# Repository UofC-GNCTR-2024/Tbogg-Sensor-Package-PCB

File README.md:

# Tbogg-Sensor-Package-PCB
The sensor package (strain, temperature, vibration) for the 2024 UofC GNCTR tbogg. Designed as an R&amp;D intrastructure monitoring solution.

## Main Components

1. **2x** Strain Gauge Blocks
	* Ulimately reads one of these two strain gauges:
		1. [100x BF350-3AA](https://www.aliexpress.com/item/595240806.html)
		2. [10x BX120-2AA](https://www.aliexpress.com/item/1005003672107724.html)
	* Based on [this schematic](https://www.elecrow.com/strain-gauge-module-p-735.html)
	* Sensing via HX711 chip
2. **1x** On-PCB Temperature Sensor (STDS75DS2F)
	* I2C
3. **2x** In-Concrete Temperature Sensors
	* Thermistor-based
4. **1x** Vibration Sensor
	* Model: MPU-6050 Breakout
	* I2C Comms
5. I2C Optical Flow Sensor
6. Battery: 4x 18650
	* TODO: choose quantity, model, holder, and connection
	* In series
7. Battery Management System: probably the 3V3 buck-boost from the balloon project
	* TODO: more info
8. Wireless Comms: LoRa Wio E5
	* TODO: pull from balloon project
	* TODO: confirm that this model is good
9. Microcontroller Unit (MCU)
	* ESP32 Breakout

## Reference Links
* TODO: fill

## Revision Notes
* PCB orders will each recieve a new revision number. 
	* PCB orders will be in the format of "Rev1", "Rev2", etc.
	* GitHub Releases (and Tags) will be tagged in the format of `rev1`, `rev2`, etc.
* BOM changes on PCB orders should be documented as minor revisions.
	* Example: `rev1.1`, `rev1.2`, etc.

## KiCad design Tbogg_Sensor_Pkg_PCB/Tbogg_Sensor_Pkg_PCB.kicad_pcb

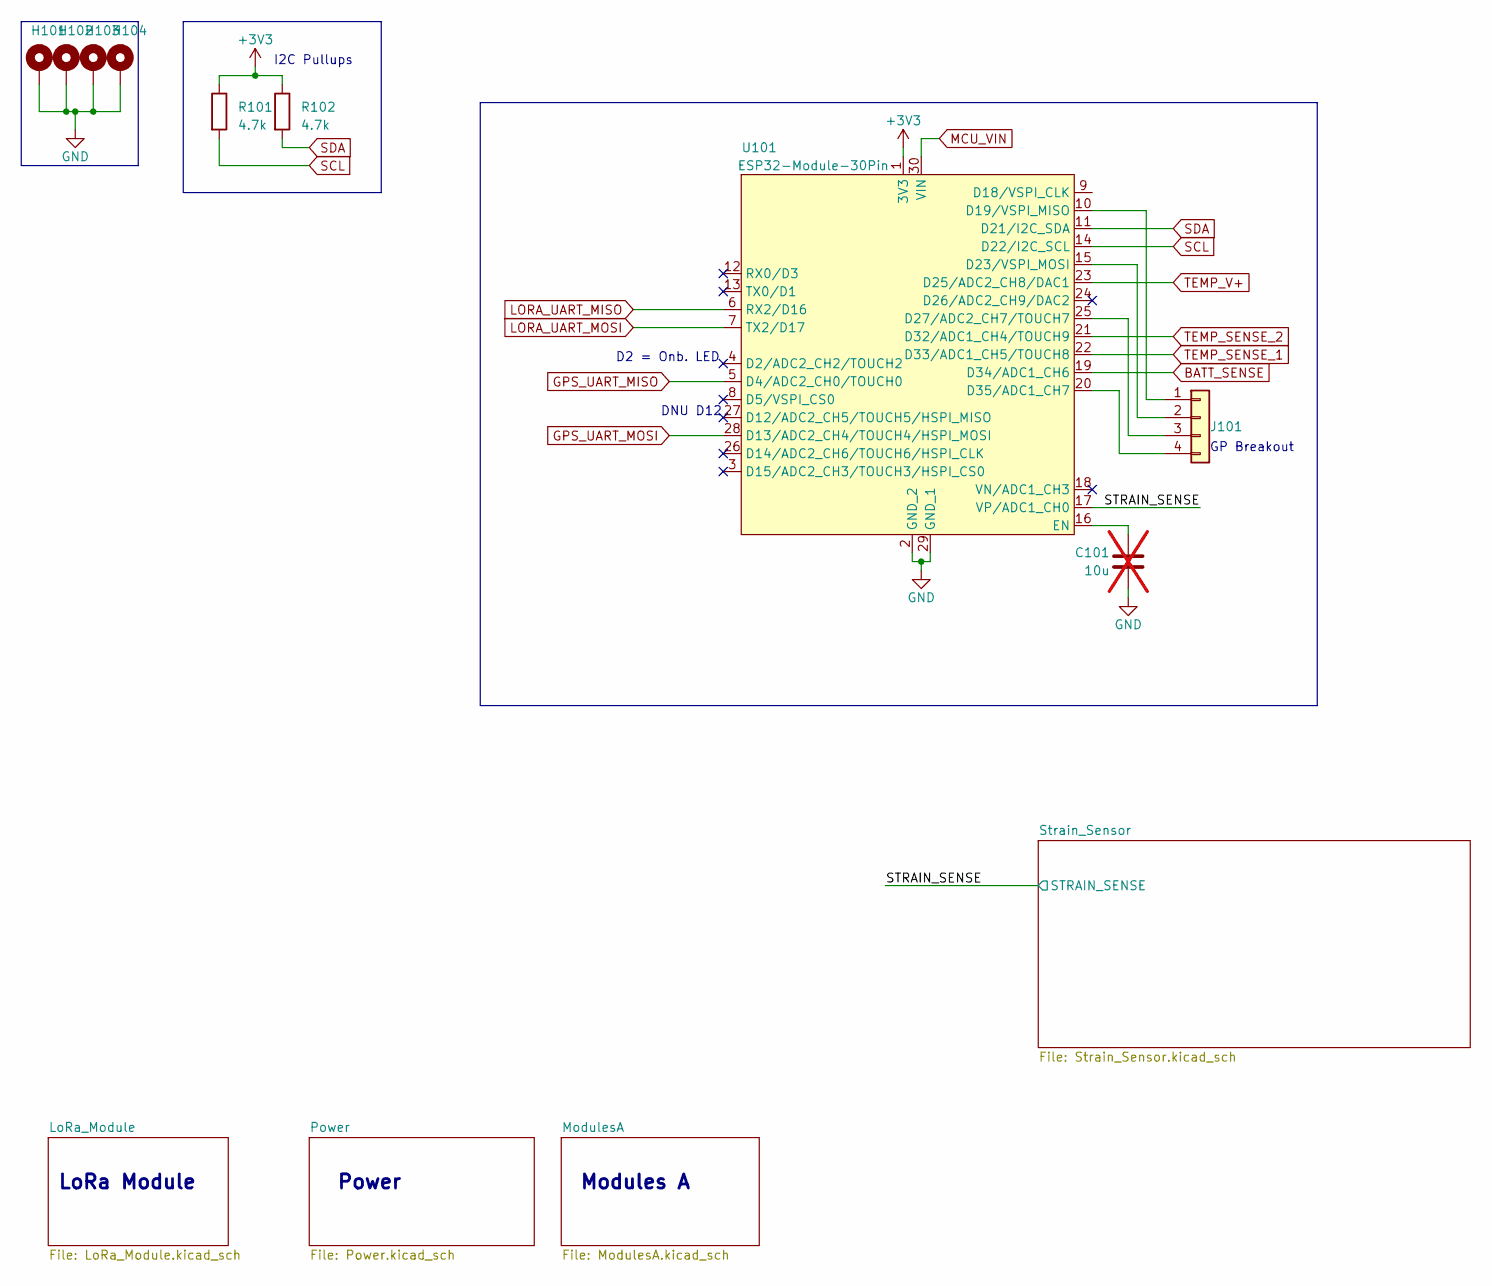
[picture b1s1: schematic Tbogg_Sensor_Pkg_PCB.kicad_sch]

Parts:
C101: 10u; C_1206_3216Metric_Pad1.33x1.80mm_HandSolder; not fitted
H101, H102, H103, H104: MountingHole_Pad; MountingHole_3.2mm_M3_DIN965_Pad
J101: Conn_01x04; PinHeader_1x04_P2.54mm_Vertical
R101, R102: 4.7k; R_1206_3216Metric_Pad1.30x1.75mm_HandSolder
U101: ESP32-Module-30Pin

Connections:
BATT_SENSE: U101.19 (D34/ADC1_CH6); also elsewhere on the board
GND: C101.2, H101.1, H102.1, H103.1, H104.1, U101.2 (GND_2), U101.29 (GND_1); also elsewhere on the board
GPS_UART_MISO: U101.5 (D4/ADC2_CH0/TOUCH0); also elsewhere on the board
GPS_UART_MOSI: U101.28 (D13/ADC2_CH4/TOUCH4/HSPI_MOSI); also elsewhere on the board
LORA_UART_MISO: U101.6 (RX2/D16); also elsewhere on the board
LORA_UART_MOSI: U101.7 (TX2/D17); also elsewhere on the board
MCU_VIN: U101.30 (VIN); also elsewhere on the board
unnamed: J101.1, U101.10 (D19/VSPI_MISO)
unnamed: J101.2, U101.15 (D23/VSPI_MOSI)
unnamed: J101.3, U101.25 (D27/ADC2_CH7/TOUCH7)
unnamed: J101.4, U101.20 (D35/ADC1_CH7)
unnamed: C101.1, U101.16 (EN)
SCL: R101.2, U101.14 (D22/I2C_SCL); also elsewhere on the board
SDA: R102.2, U101.11 (D21/I2C_SDA); also elsewhere on the board
TEMP_SENSE_1: U101.22 (D33/ADC1_CH5/TOUCH8); also elsewhere on the board
TEMP_SENSE_2: U101.21 (D32/ADC1_CH4/TOUCH9); also elsewhere on the board
TEMP_V+: U101.23 (D25/ADC2_CH8/DAC1); also elsewhere on the board

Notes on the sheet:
LoRa Module
GP Breakout
D2 = Onb. LED
Modules A
DNU D12
Power
I2C Pullups

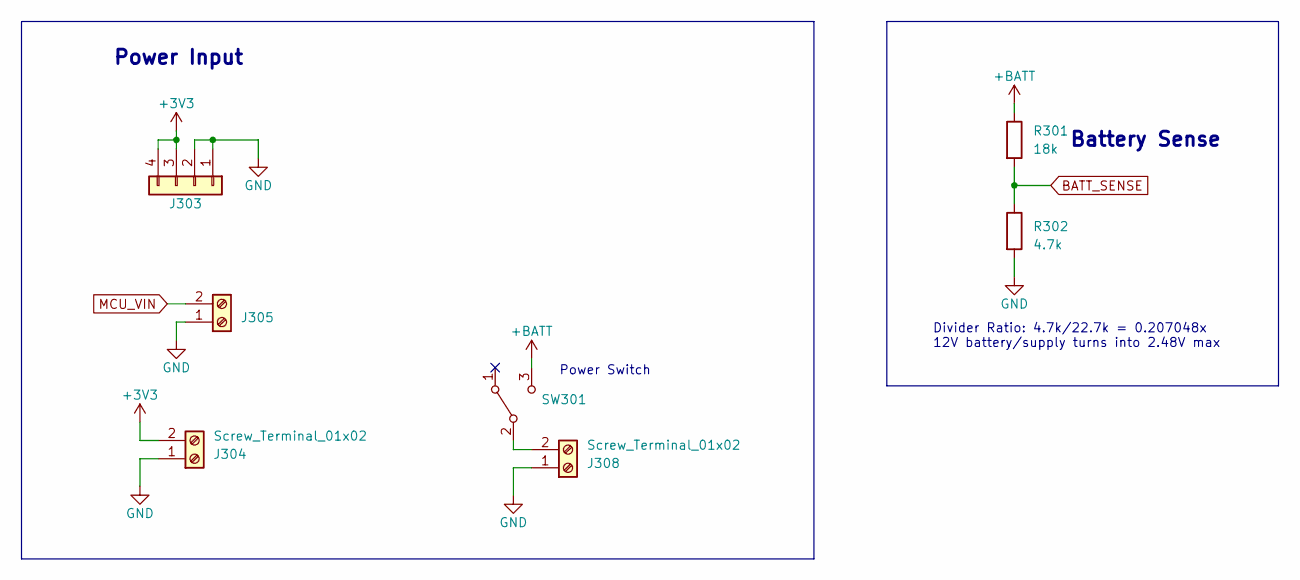
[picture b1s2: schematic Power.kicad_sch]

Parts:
J303: Conn_01x04; PinHeader_1x04_P2.54mm_Vertical
J304, J305, J308: Screw_Terminal_01x02; TerminalBlock_bornier-2_P5.08mm
R301: 18k; R_1206_3216Metric_Pad1.30x1.75mm_HandSolder
R302: 4.7k; R_1206_3216Metric_Pad1.30x1.75mm_HandSolder
SW301: SW_SPDT; SW_Slide_1P2T_CK_OS102011MS2Q

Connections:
+BATT: R301.1, SW301.3 (C)
BATT_SENSE: R301.2, R302.1; also elsewhere on the board
GND: J303.1, J303.2, J304.1, J305.1, J308.1, R302.2; also elsewhere on the board
MCU_VIN: J305.2; also elsewhere on the board
unnamed: J308.2, SW301.2 (B)

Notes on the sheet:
Divider Ratio: 4.7k/22.7k = 0.207048x 12V battery/supply turns into 2.48V max
Power Switch
Battery Sense
Power Input

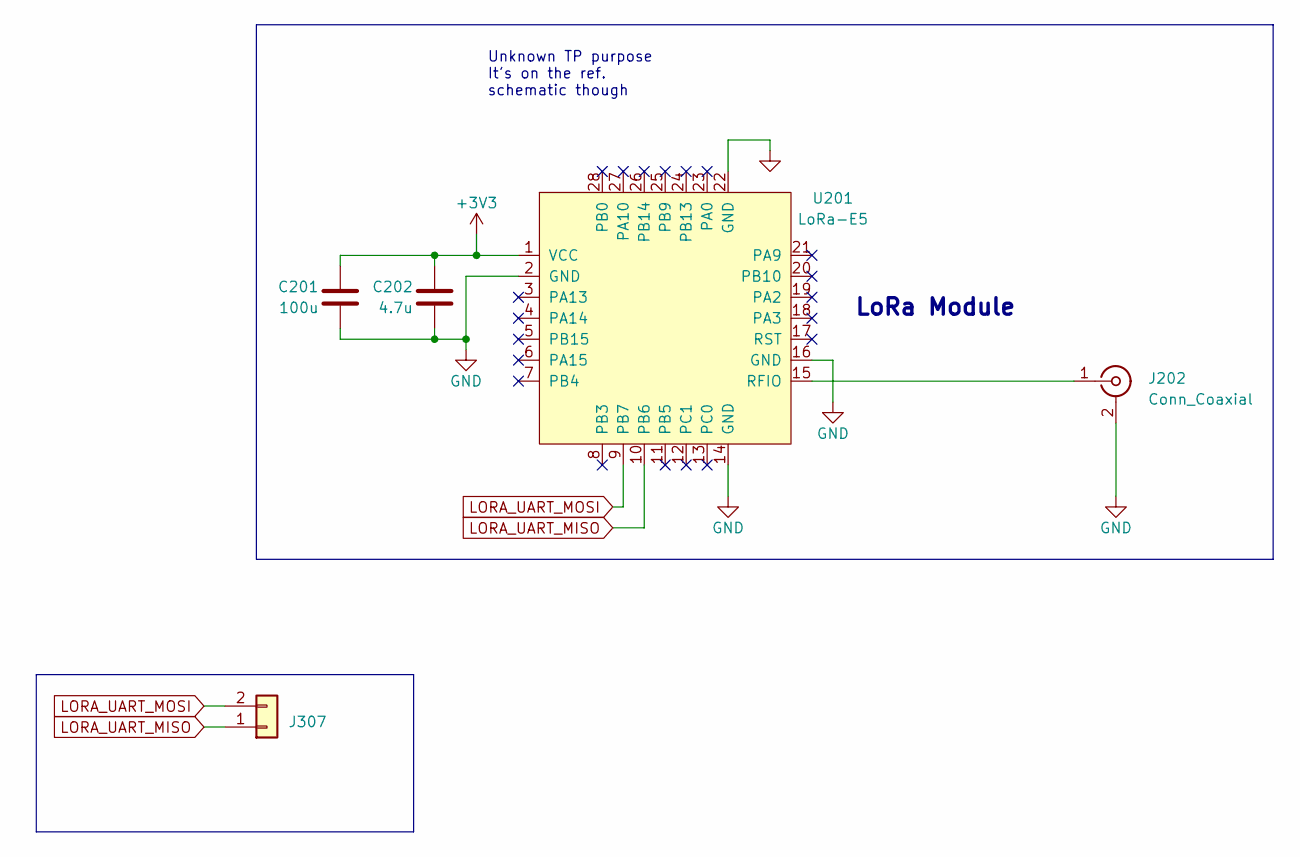
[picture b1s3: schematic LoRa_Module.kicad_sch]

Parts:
C201: 100u; C_1206_3216Metric_Pad1.33x1.80mm_HandSolder
C202: 4.7u; C_1206_3216Metric_Pad1.33x1.80mm_HandSolder
J202: Conn_Coaxial; SMA_Wurth_60312002114503_Vertical
J307: Conn_01x02; PinHeader_1x02_P2.54mm_Vertical
U201: LoRa-E5; LoRa-E5_HandSolder

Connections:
GND: C201.2, C202.2, J202.2 (Ext), U201.2 (GND), U201.14 (GND), U201.16 (GND), U201.22 (GND); also elsewhere on the board
LORA_UART_MISO: U201.10 (PB6); also elsewhere on the board
LORA_UART_MOSI: U201.9 (PB7); also elsewhere on the board
unnamed: J202.1 (In), U201.15 (RFIO)

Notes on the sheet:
Unknown TP purpose It's on the ref. schematic though
LoRa Module

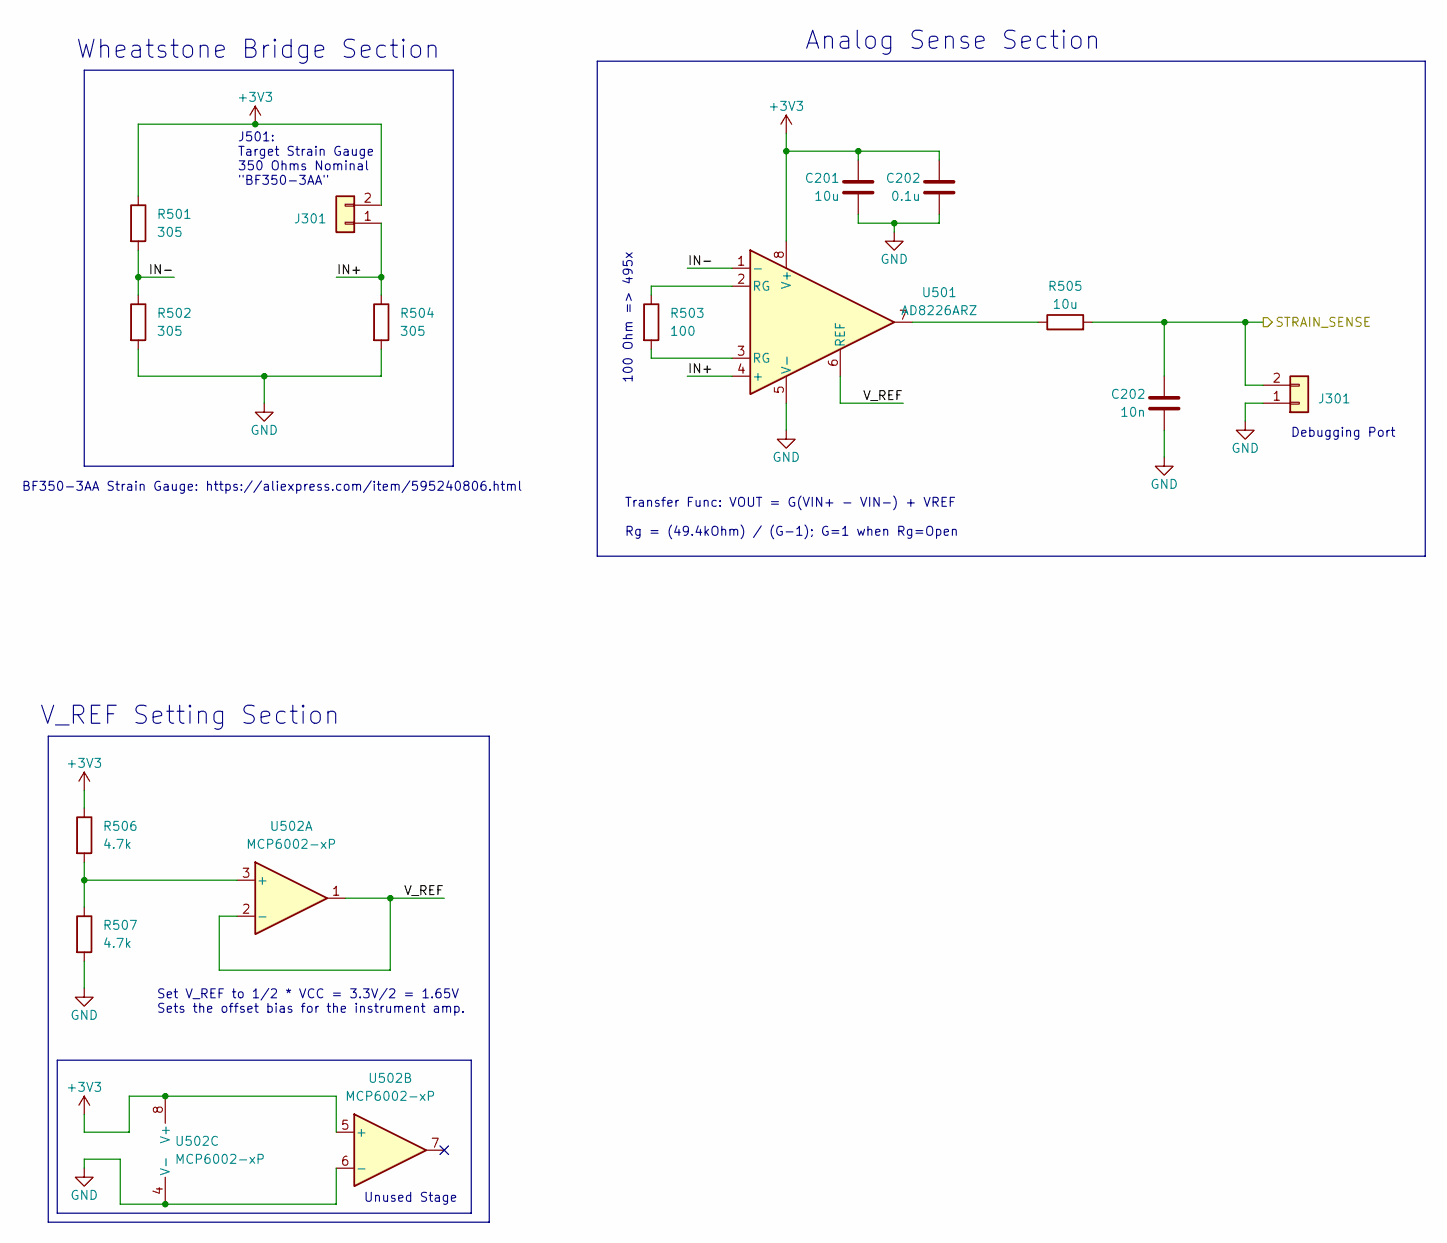
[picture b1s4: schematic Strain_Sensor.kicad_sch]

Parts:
C201: 10u; C_1206_3216Metric_Pad1.33x1.80mm_HandSolder
C202: 0.1u; C_1206_3216Metric_Pad1.33x1.80mm_HandSolder
J301: Conn_01x02; PinHeader_1x02_P2.54mm_Vertical
R501, R502, R504: 305; InactiveStrainGauge
R503: 100; R_1206_3216Metric_Pad1.30x1.75mm_HandSolder
R505: 10u; R_1206_3216Metric_Pad1.30x1.75mm_HandSolder
R506, R507: 4.7k; R_1206_3216Metric_Pad1.30x1.75mm_HandSolder
U501: AD8226ARZ; SO-8_3.9x4.9mm_P1.27mm
U502: MCP6002-xP; DIP-8_W7.62mm_LongPads

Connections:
/Strain_Sensor/IN+: R504.1, U501.4 (+); also elsewhere on the board
/Strain_Sensor/IN-: R501.2, R502.1, U501.1 (-)
/Strain_Sensor/V_REF: U501.6 (REF), U502.1, U502.2 (-)
GND: C201.2, C202.2, R502.2, R504.2, R507.2, U501.5 (V-), U502.4 (V-), U502.6 (-); also elsewhere on the board
unnamed: R503.1, U501.2 (RG)
unnamed: R503.2, U501.3 (RG)
unnamed: R505.1, U501.7
unnamed: R506.2, R507.1, U502.3 (+)

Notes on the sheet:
Unused Stage
J501: Target Strain Gauge 350 Ohms Nominal "BF350-3AA"
Debugging Port
V_REF Setting Section
Transfer Func: VOUT = G(VIN+ − VIN−) + VREF Rg = (49.4kOhm) / (G-1); G=1 when Rg=Open
100 Ohm => 495x
BF350-3AA Strain Gauge: https://aliexpress.com/item/595240806.html
Set V_REF to 1/2 * VCC = 3.3V/2 = 1.65V Sets the offset bias for the instrument amp.
Wheatstone Bridge Section
Analog Sense Section

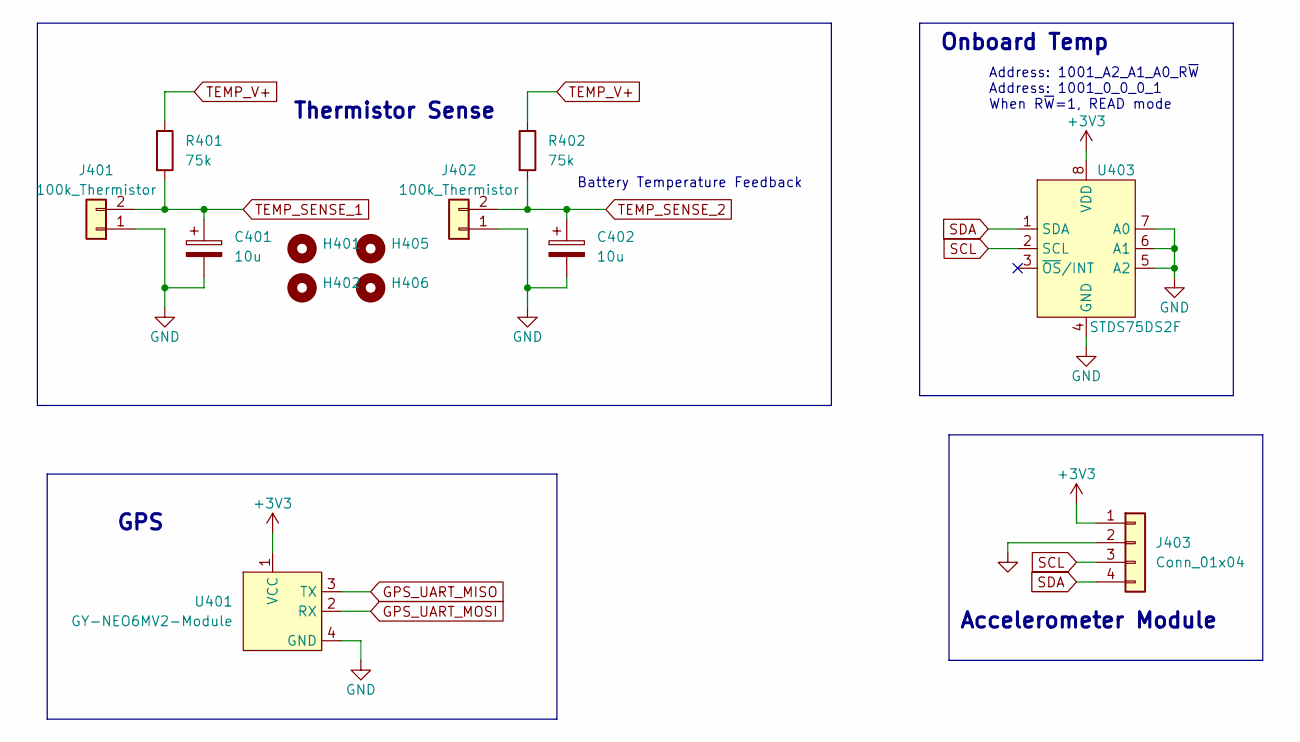
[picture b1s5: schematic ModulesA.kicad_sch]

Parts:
C401, C402: 10u; C_1206_3216Metric_Pad1.33x1.80mm_HandSolder
H401, H402, H405, H406: MountingHole; MountingHole_2mm
J401, J402: 100k_Thermistor; PinHeader_1x02_P2.54mm_Vertical
J403: Conn_01x04; PinHeader_1x04_P2.54mm_Vertical
R401, R402: 75k; R_1206_3216Metric_Pad1.30x1.75mm_HandSolder
U401: GY-NEO6MV2-Module
U403: STDS75DS2F; MSOP-8_3x3mm_P0.65mm; LCSC C283289

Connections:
GND: C401.2, C402.2, J401.1, J402.1, J403.2, U401.4 (GND), U403.4 (GND), U403.5 (A2), U403.6 (A1), U403.7 (A0); also elsewhere on the board
GPS_UART_MISO: U401.3 (TX); also elsewhere on the board
GPS_UART_MOSI: U401.2 (RX); also elsewhere on the board
SCL: J403.3, U403.2 (SCL); also elsewhere on the board
SDA: J403.4, U403.1 (SDA); also elsewhere on the board
TEMP_SENSE_1: C401.1, J401.2, R401.2; also elsewhere on the board
TEMP_SENSE_2: C402.1, J402.2, R402.2; also elsewhere on the board
TEMP_V+: R401.1, R402.1; also elsewhere on the board

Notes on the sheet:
Accelerometer Module
Onboard Temp
Address: 1001_A2_A1_A0_R~{W} Address: 1001_0_0_0_1 When R~{W}=1, READ mode
GPS
Thermistor Sense
Battery Temperature Feedback

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
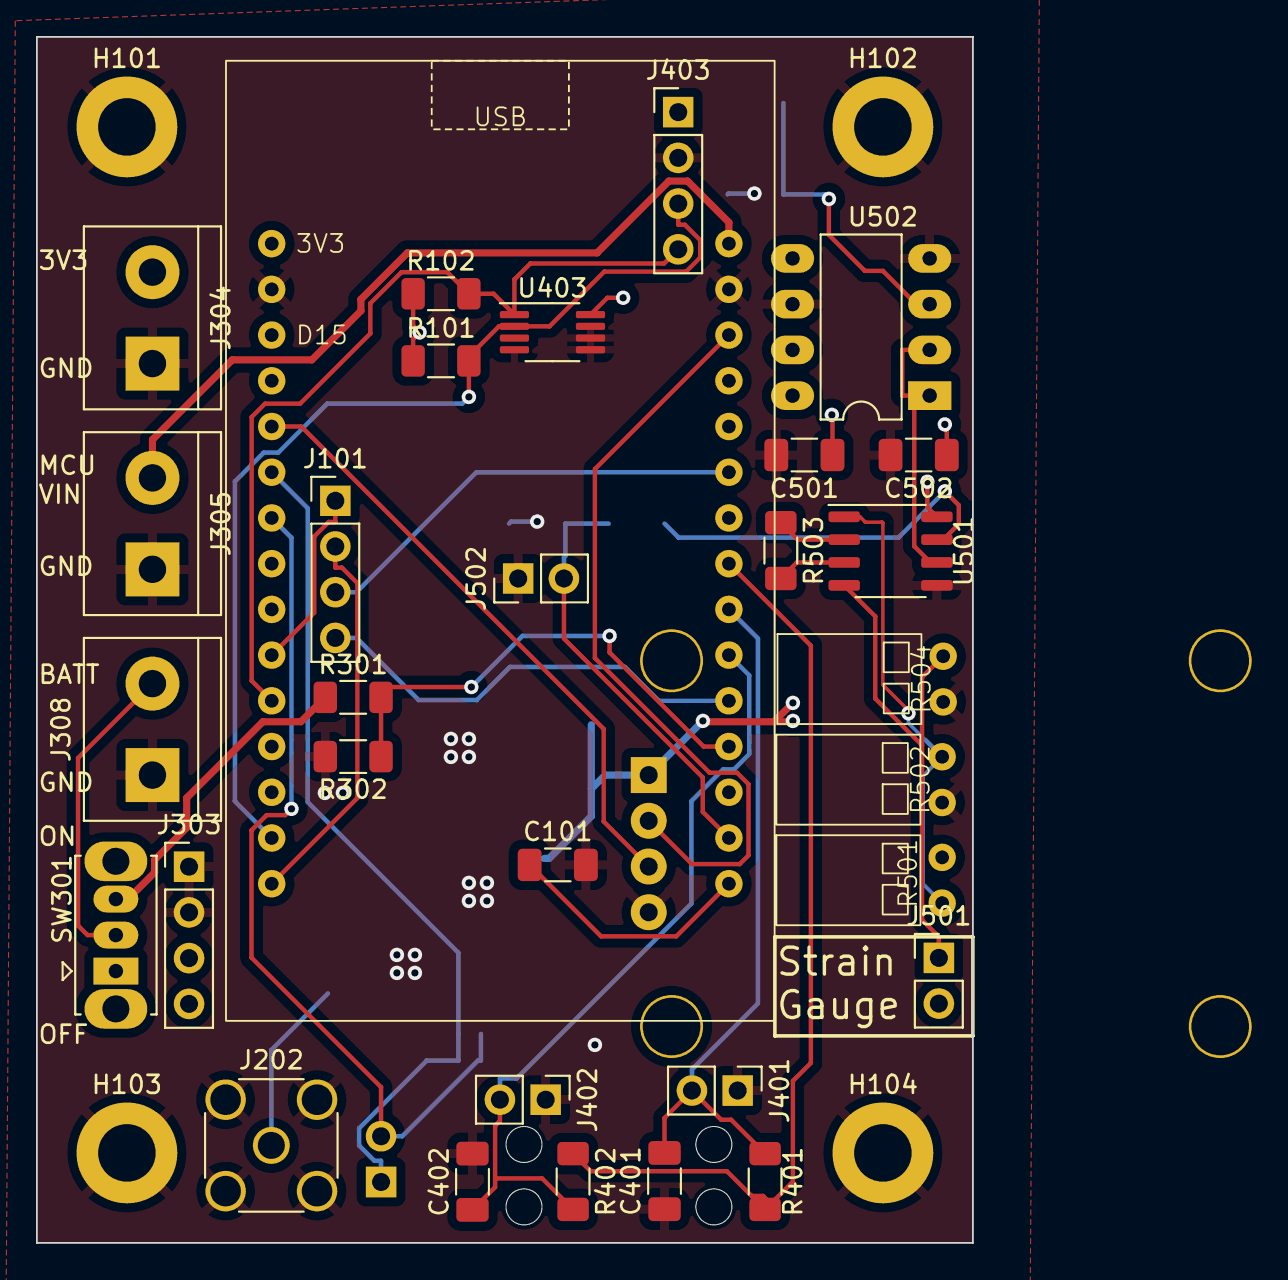
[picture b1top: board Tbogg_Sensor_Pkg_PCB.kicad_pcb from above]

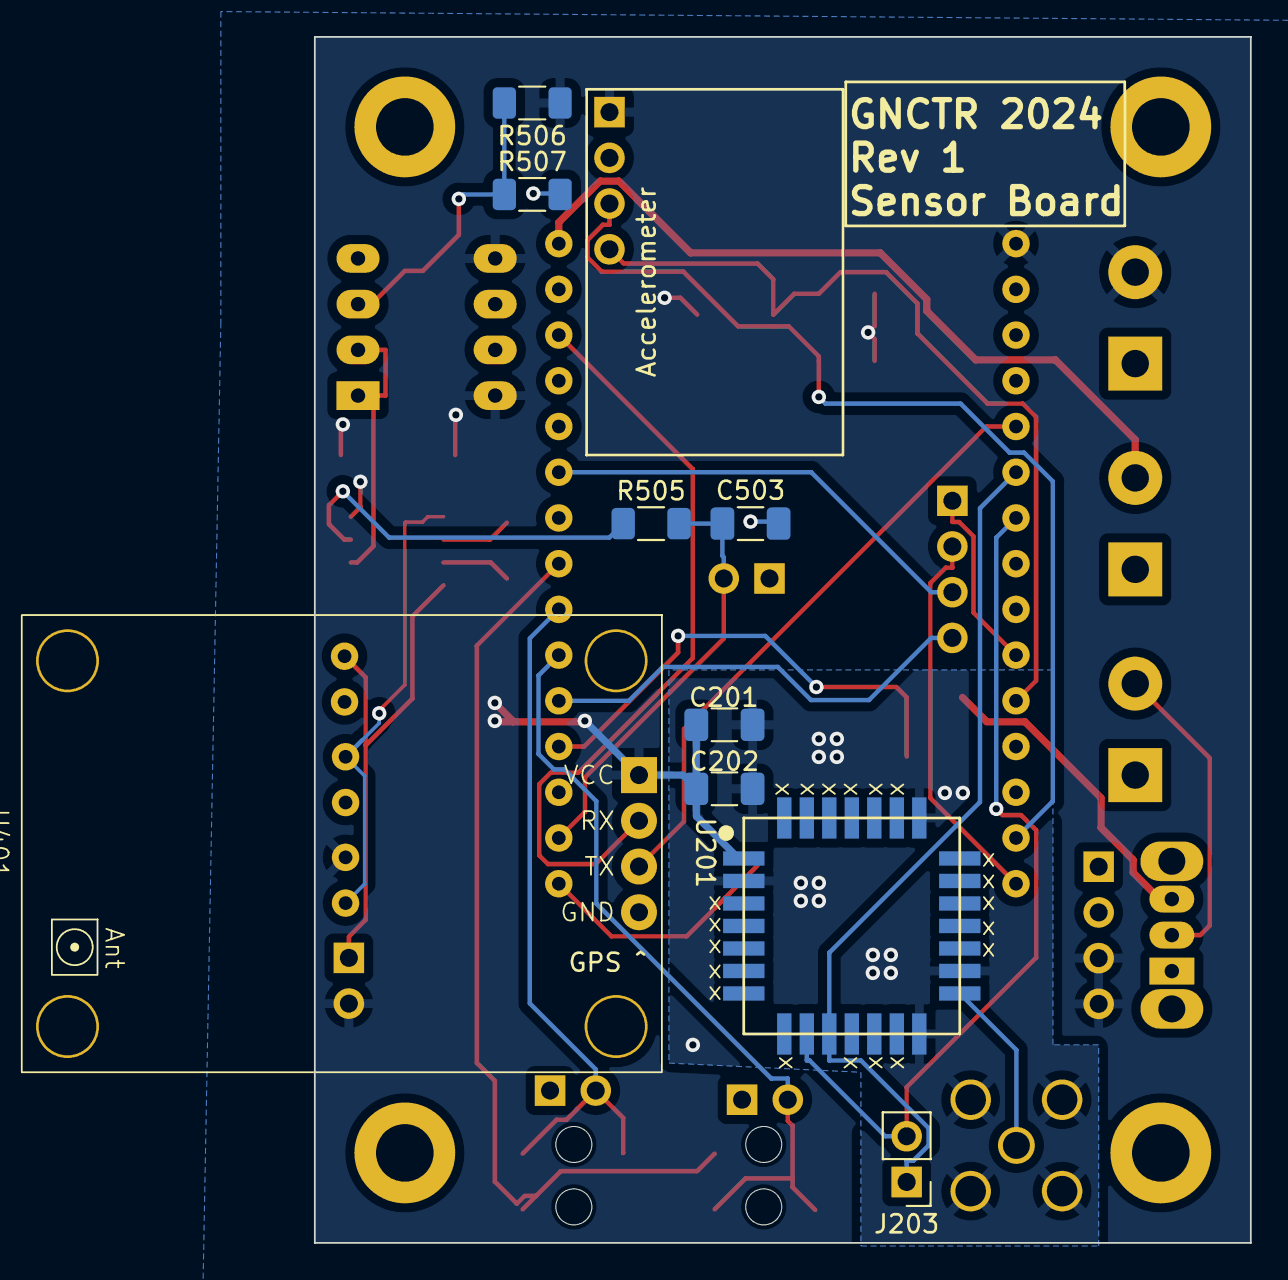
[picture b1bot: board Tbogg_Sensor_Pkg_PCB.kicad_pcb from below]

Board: 2 copper layers, 52.0 x 67.0 mm, 48 parts (9 on the bottom side), 29 nets.

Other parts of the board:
C501: 10u; C_1206_3216Metric_Pad1.33x1.80mm_HandSolder
C502: 0.1u; C_1206_3216Metric_Pad1.33x1.80mm_HandSolder
C503: 10n; C_1206_3216Metric_Pad1.33x1.80mm_HandSolder
J203, J501, J502: Conn_01x02; PinHeader_1x02_P2.54mm_Vertical

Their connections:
/Strain_Sensor/IN+: J501.1; also elsewhere on the board
GND: C501.2, C502.2, C503.2, J502.1; also elsewhere on the board
LORA_UART_MISO: J203.1; also elsewhere on the board
LORA_UART_MOSI: J203.2; also elsewhere on the board

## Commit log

2023-11-06 Add project spec to README
2023-11-06 Add starting point repo
2023-12-31 Add base from other project
2024-01-01 Finish design
2024-01-01 Tiny reroutes, labels
2024-01-01 Export Rev1 Gerber
2024-01-02 Plot rev1 schematic with rev number
2024-01-05 Load base YAPP v3.0.0 enclosure design
2024-01-06 Create simple ESP32 doit enclosure (bad USB placement though)
2024-01-08 Fix USB hole alignment
2024-01-08 Center the snapJoins
2024-01-11 Fix padding around USB port
2024-01-23 Bump enclosure template version to v3.0.1
2024-01-23 Create shell structure for enclosure
2024-01-23 Comments updates
2024-02-26 Create light/motion enclosure
2024-02-26 Switch pin from base to lid (and bump lib version)
2024-02-27 Fix enclosure dimensions
2024-02-27 Fix enclosure dimension on PCB comments layer
2024-02-28 Tiny tweaks, antenna
2024-03-03 Increase light sensor diameter
